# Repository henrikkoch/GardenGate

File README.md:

# GardenGatePCB
Garden Gate PCB

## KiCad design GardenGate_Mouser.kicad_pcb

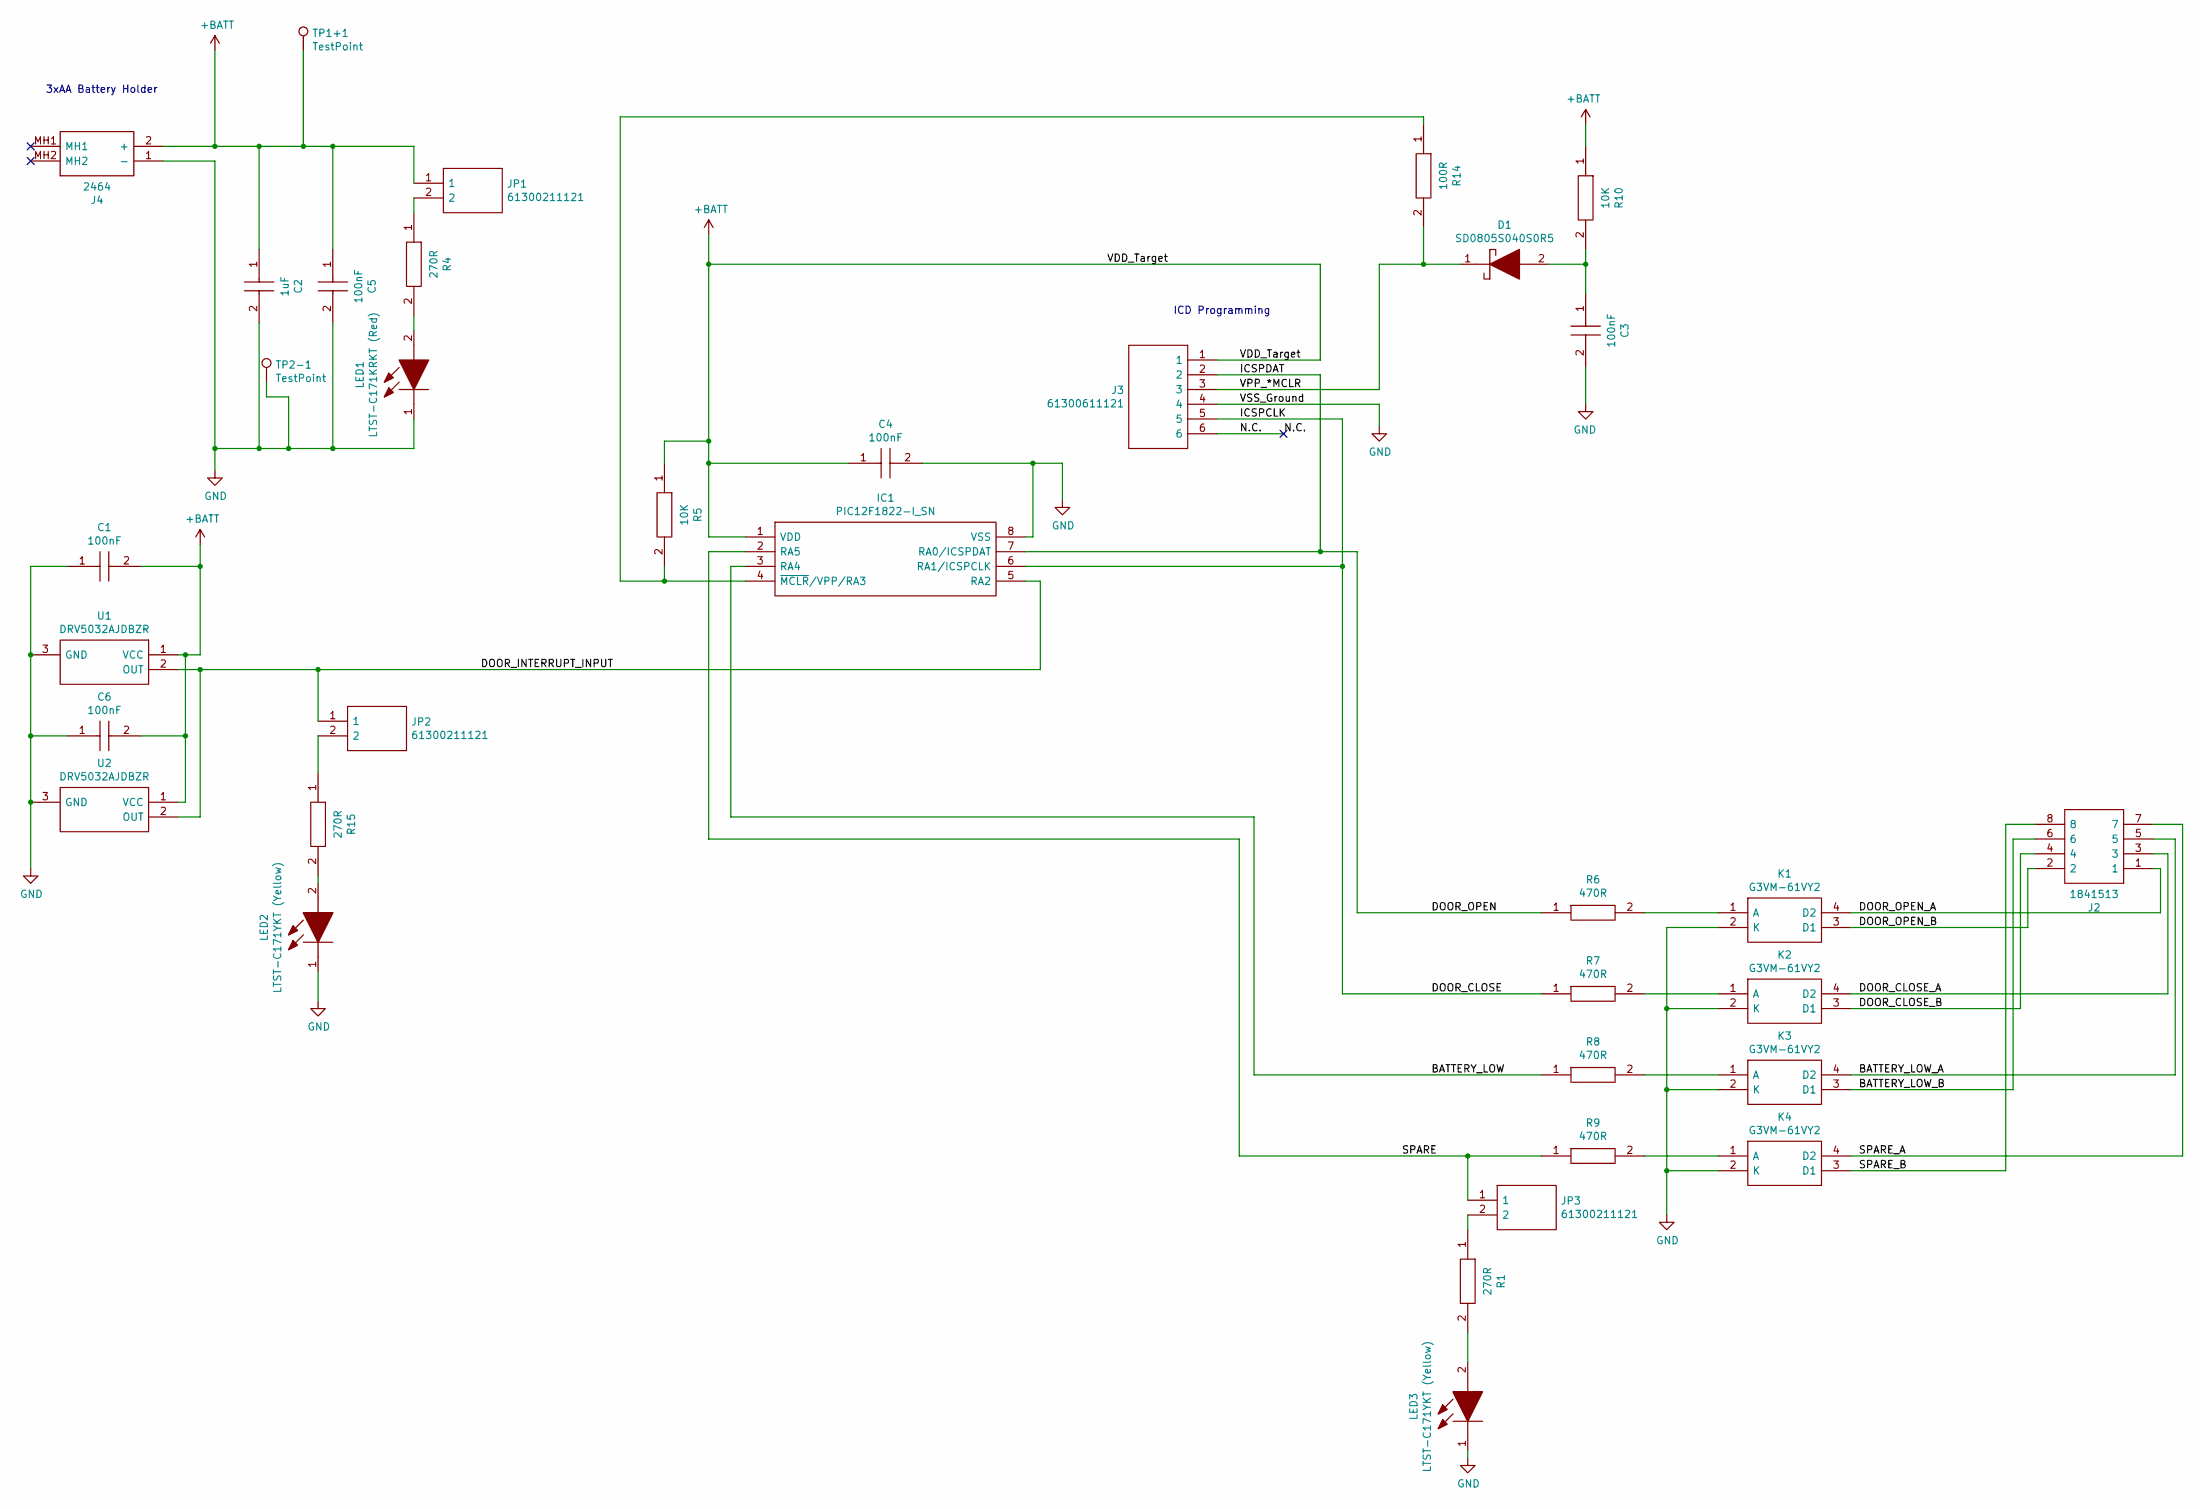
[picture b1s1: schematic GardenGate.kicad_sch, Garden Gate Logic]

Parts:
C1, C3, C4, C5, C6: 100nF; CAPC2012X88N; Mouser Part Number 80-C0805C104K5RACLR
C2: 1uF; CAPC2012X135N; Mouser Part Number 963-UMF212B7105KGHT
D1: SD0805S040S0R5; SD0805; Mouser Part Number 581-SD0805S040S0R5
IC1: PIC12F1822-I_SN; SOIC127P600X175-8N; Mouser Part Number 579-PIC12F1822-I/SN
J2: 1841513; SHDR8W110P935X350_2X4_1550X1800X2440P; Mouser Part Number 651-1841513
J3: 61300611121; HDRV6W64P0X254_1X6_1524X254X869P; Mouser Part Number 710-61300611121
J4: 2464; Mouser Part Number 534-2464
JP1, JP2, JP3: 61300211121; HDRV2W110P0X254_1X2_508X254X854P; Mouser Part Number 710-61300211121
K1, K2, K3, K4: G3VM-61VY2; SOP254P700X230-4N; Mouser Part Number 653-G3VM61VY2
LED1: LTST-C171KRKT (Red); GardenGateLED; Mouser Part Number 859-LTST-C171KRKT
LED2, LED3: LTST-C171YKT (Yellow); GardenGateLED; Mouser Part Number 859-LTST-C171YKT
R1, R4, R15: 270R; RESC2012X60N; Mouser Part Number 603-RC0805FR-07270RL
R5, R10: 10K; RESC2012X60N; Mouser Part Number 603-RC0805JR-0710KL
R6, R7, R8, R9: 470R; RESC2012X60N; Mouser Part Number 603-RC0805JR-10470RL
R14: 100R; RESC2012X60N; Mouser Part Number 603-RC0805JR-100RL
TP1+1, TP2-1: TestPoint; TestPoint_Pad_D3.0mm
U1, U2: DRV5032AJDBZR; TO-92_Molded_Narrow; Manufacturer_Part_Number DRV5032AJDBZR; Mouser Part Number 595-DRV5032AJDBZR

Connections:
+BATT: C1.2, C2.1, C4.1, C5.1, C6.2, IC1.1 (VDD), J3.1, J4.2 (+), JP1.1, R5.1, R10.1, TP1+1.1, U1.1 (VCC), U2.1 (VCC)
/BATTERY_LOW: IC1.3 (RA4), R8.1
/BATTERY_LOW_A: J2.5, K3.4 (D2)
/BATTERY_LOW_B: J2.6, K3.3 (D1)
/DOOR_CLOSE: IC1.6 (RA1/ICSPCLK), J3.5, R7.1
/DOOR_CLOSE_A: J2.3, K2.4 (D2)
/DOOR_CLOSE_B: J2.4, K2.3 (D1)
/DOOR_INTERRUPT_INPUT: IC1.5 (RA2), JP2.1, U1.2 (OUT), U2.2 (OUT)
/DOOR_OPEN: IC1.7 (RA0/ICSPDAT), J3.2, R6.1
/DOOR_OPEN_A: J2.1, K1.4 (D2)
/DOOR_OPEN_B: J2.2, K1.3 (D1)
/N.C.: J3.6
/SPARE: IC1.2 (RA5), JP3.1, R9.1
/SPARE_A: J2.7, K4.4 (D2)
/SPARE_B: J2.8, K4.3 (D1)
/VPP_*MCLR: D1.1, J3.3, R14.2
GND: C1.1, C2.2, C3.2, C4.2, C5.2, C6.1, IC1.8 (VSS), J3.4, J4.1 (-), K1.2 (K), K2.2 (K), K3.2 (K), K4.2 (K), LED1.1, LED2.1, LED3.1, TP2-1.1, U1.3 (GND), U2.3 (GND)
unnamed: C3.1, D1.2, R10.2
unnamed: IC1.4 (~MCLR/VPP/RA3), R5.2, R14.1
unnamed: JP1.2, R4.1
unnamed: JP2.2, R15.1
unnamed: JP3.2, R1.1
unnamed: K1.1 (A), R6.2
unnamed: K2.1 (A), R7.2
unnamed: K3.1 (A), R8.2
unnamed: K4.1 (A), R9.2
unnamed: LED1.2, R4.2
unnamed: LED2.2, R15.2
unnamed: LED3.2, R1.2

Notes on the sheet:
ICD Programming
3xAA Battery Holder

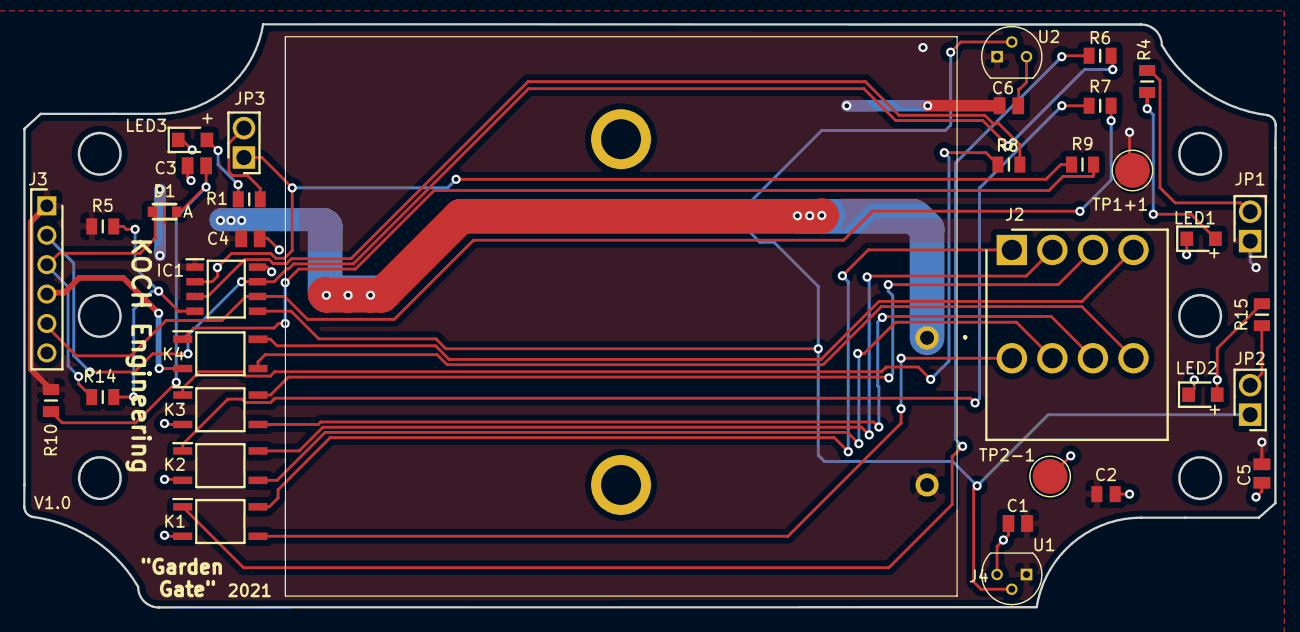
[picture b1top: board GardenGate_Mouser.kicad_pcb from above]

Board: 2 copper layers, 108.0 x 50.3 mm, 35 parts (0 on the bottom side), 28 nets.

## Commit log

2022-08-04 First version from Zip file
    This is my first full version from the zip file backup
2022-08-04 A new commit with all the files from the KiCad folder
    This means that some files from the Zip file has now been over written
2022-08-04 Clean up and going back to the zip file version
2022-08-04 going back to the Zip files version to clean-up
2022-08-04 Files from the Version 1 (from the KiCad folder)
    All files from KiCad folder containing version 1.0
2022-08-04 version 1.0.1
    PCB version 1.0. all files added to here
